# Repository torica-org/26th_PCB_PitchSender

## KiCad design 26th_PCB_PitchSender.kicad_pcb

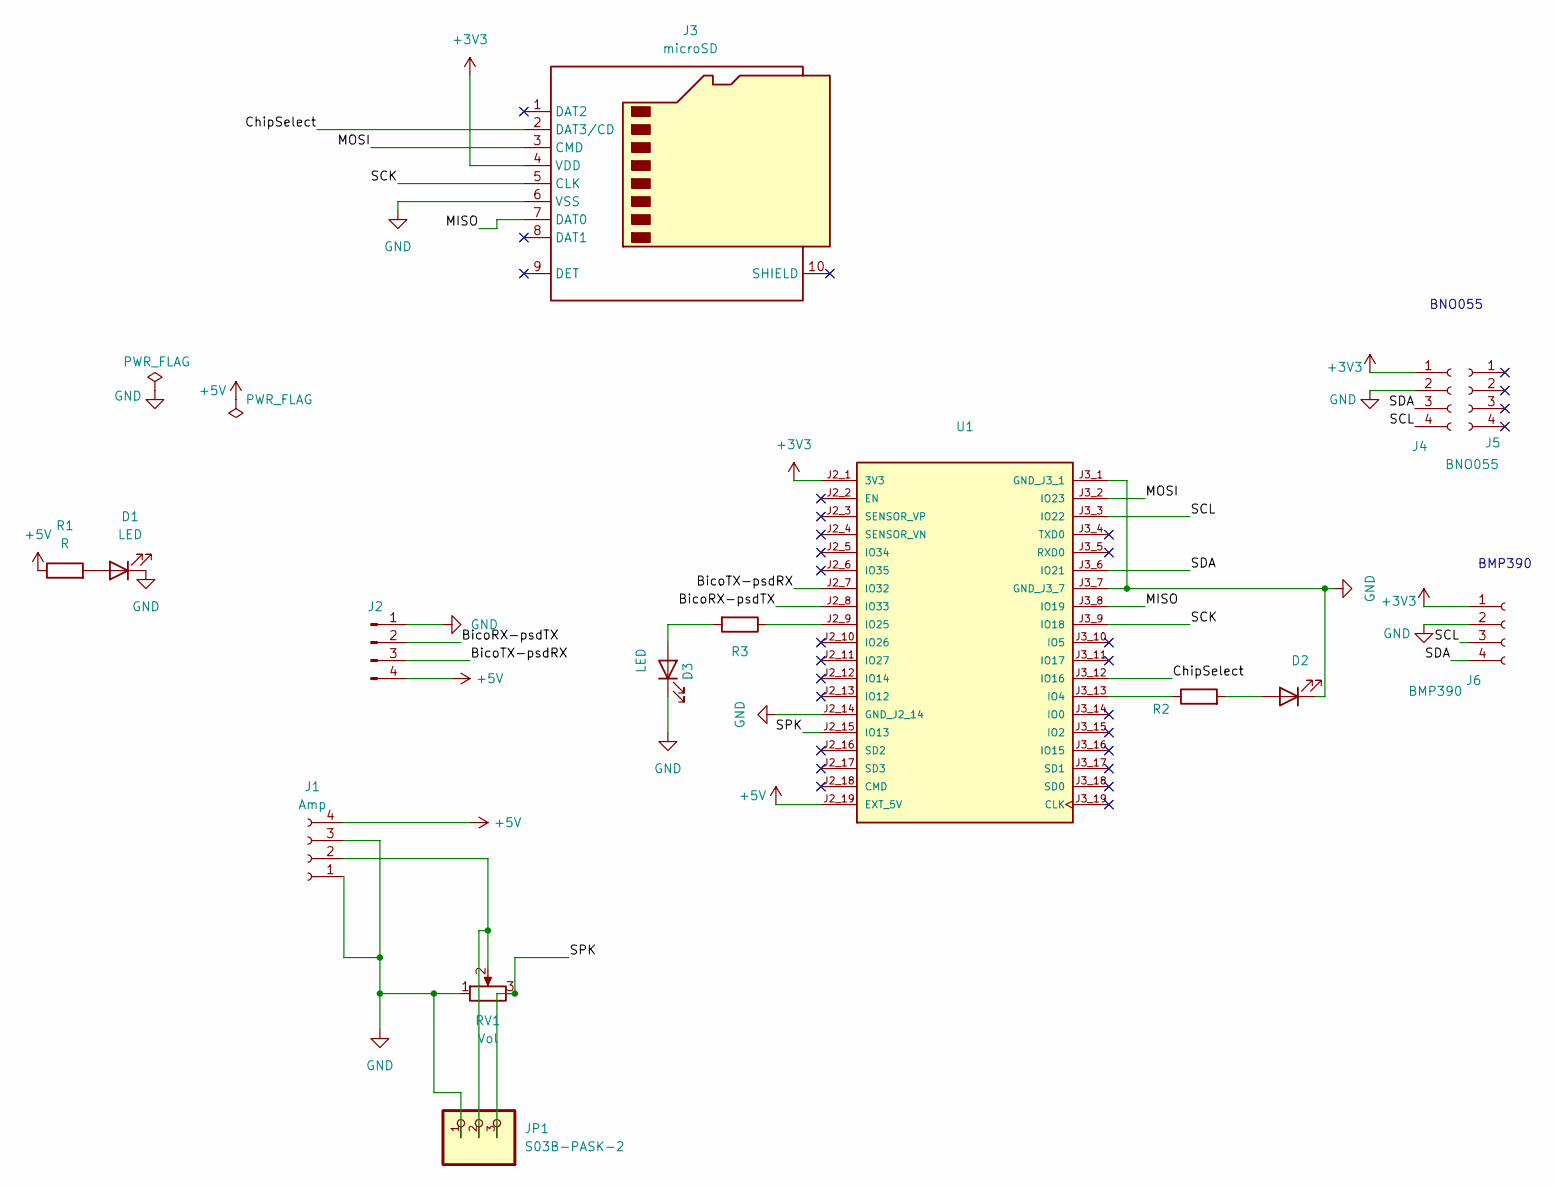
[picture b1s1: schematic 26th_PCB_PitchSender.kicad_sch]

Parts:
D1, D2, D3: LED; LED_D3.0mm
J1: Amp; PinHeader_1x04_P2.54mm_Vertical
J2: Conn_01x04_Pin; JST_S04B-PASK-2_LF__SN_
J3: microSD; PinHeader_1x10_P2.54mm_Vertical
J4: Conn_01x04_Socket; PinHeader_1x04_P2.54mm_Vertical
J5: BNO055; PinHeader_1x04_P2.54mm_Vertical
J6: BMP390; PinHeader_1x04_P2.54mm_Vertical
JP1: S03B-PASK-2
R1, R2, R3: R; R_Axial_DIN0204_L3.6mm_D1.6mm_P5.08mm_Horizontal
RV1: Vol; PinHeader_1x03_P2.54mm_Vertical
U1: MODULE_ESP32-DEVKITC-32E; PARTREV 1.4

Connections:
+3V3: J3.4 (VDD), J4.1, J6.1, U1.J2_1 (3V3)
+5V: J1.4, J2.4, R1.1, U1.J2_19 (EXT_5V)
/BicoRX-psdTX: J2.2, U1.J2_8 (IO33)
/BicoTX-psdRX: J2.3, U1.J2_7 (IO32)
/ChipSelect: J3.2 (DAT3/CD), U1.J3_12 (IO16)
/MISO: J3.7 (DAT0), U1.J3_8 (IO19)
/MOSI: J3.3 (CMD), U1.J3_2 (IO23)
/SCK: J3.5 (CLK), U1.J3_9 (IO18)
/SCL: J4.4, J6.3, U1.J3_3 (IO22)
/SDA: J4.3, J6.4, U1.J3_6 (IO21)
/SPK: JP1.3, RV1.3, U1.J2_15 (IO13)
GND: D1.1 (K), D2.1 (K), D3.1 (K), J1.1, J1.3, J2.1, J3.6 (VSS), J4.2, J6.2, JP1.1, RV1.1, U1.J2_14 (GND_J2_14), U1.J3_1 (GND_J3_1), U1.J3_7 (GND_J3_7)
unnamed: D1.2 (A), R1.2
unnamed: D2.2 (A), R2.2
unnamed: D3.2 (A), R3.2
unnamed: J1.2, JP1.2, RV1.2
unnamed: R2.1, U1.J3_13 (IO4)
unnamed: R3.1, U1.J2_9 (IO25)

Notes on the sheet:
BNO055
BMP390

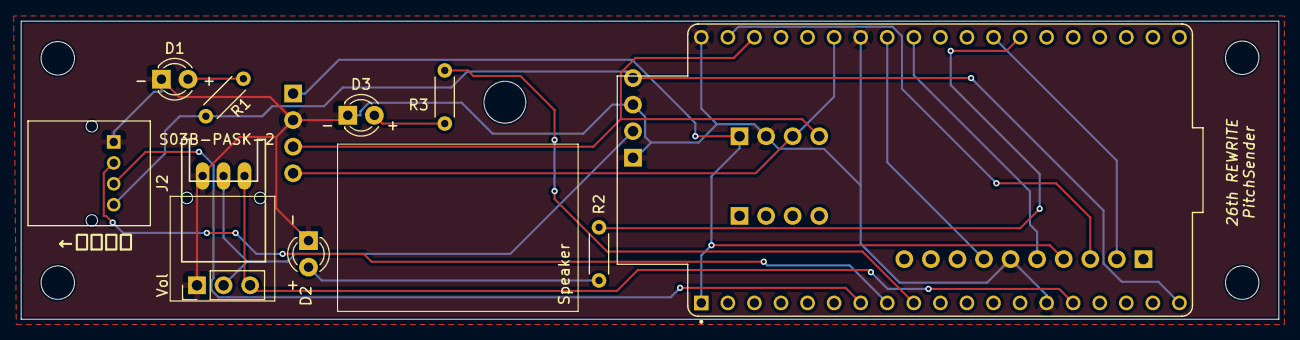
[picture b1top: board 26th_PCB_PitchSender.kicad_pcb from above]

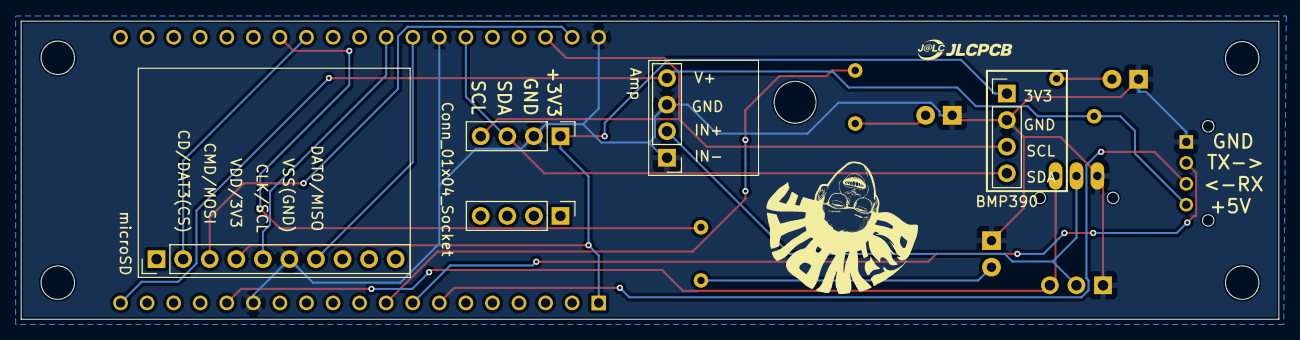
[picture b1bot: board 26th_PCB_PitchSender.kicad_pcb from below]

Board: 2 copper layers, 120.2 x 28.5 mm, 22 parts (7 on the bottom side), 18 nets.

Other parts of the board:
H1, H2, H3, H4, H5: MountingHole_3.2mm_M3
JLCPCB_LOGO: LOGO; JLCPCB(9mm)
REWRITE_LOGO: LOGO; REWRITE_LOGO

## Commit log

2026-05-26 一応完成
2026-05-26 BMP追加
2026-05-28 Add PA connecter
2026-05-29 Change SPK pin
